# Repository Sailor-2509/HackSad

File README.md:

# HackSad
a kibord for playing blox fruit

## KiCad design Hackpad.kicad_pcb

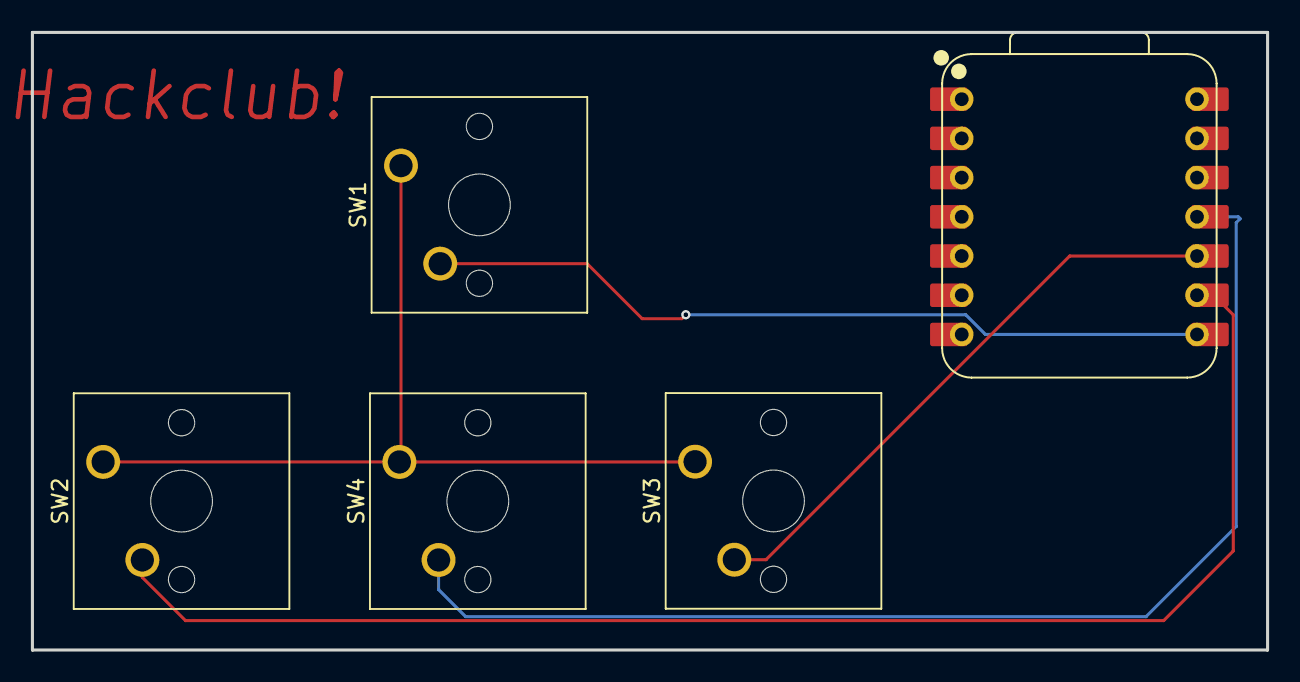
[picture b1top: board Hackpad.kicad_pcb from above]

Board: 2 copper layers, 80.0 x 40.0 mm, 5 parts (0 on the bottom side), 5 nets.

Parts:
SW1, SW2, SW3, SW4: SW_Push; SW_Cherry_MX_1.00u_PCB
U1: XIAO-RP2040-DIP

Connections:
GND: SW1.1, SW2.1, SW3.1, SW4.1
unnamed: SW1.2, U1.8 (GPIO1/RX)
unnamed: SW2.2, U1.9 (GPIO2/SCK)
unnamed: SW4.2, U1.11 (GPIO3/MOSI)
unnamed: SW3.2, U1.10 (GPIO4/MISO)
